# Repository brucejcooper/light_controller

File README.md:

# Light Switch firmware
This repo consists of the code that I'm using for my own home automation light switches.

### Theory of operation

1. Devices must operate independently.  If one of these breaks, I don't want the whole house to go dark.
1. Power consumption must be minimised, especially when the light is off.
1. I must be able to control lights via a home automation system (home assistant, or equivalent)
1. It should be as cheap as possible to produce.

So the idea is that none of these devices will have WiFi or ethernet themselves.  That would consume too much current.  Instead, We will use the DALI protocol, which is baked into the transformers that I'll be using for my home.  The circuit for driving a dali signal is very simple, with the exception of isolated power (needed to make the device safe in the presence of a 220V AC wire).  All isolated power systems that I'm aware of use a large amount of quiescent current (on the order of 10s of mA).  This would overload the DALI power supply. 

# Tech notes

## Downloading AVR compiler for attiny 0 series
The default avr-gcc installed by ubuntu doesn't do the 0 series, so I'm stealing the one that Arduino uses

```bash
wget http://downloads.arduino.cc/tools/avr-gcc-7.3.0-atmel3.6.1-arduino7-x86_64-pc-linux-gnu.tar.bz2 -q -O- | bzcat | tar xv
```

This will create a avr-gcc toolchain in the directory `avr` - The Makefile is set up to use this by default.  You can also just run `make download_gcc` to get it.  I will make this query the arduino repository for the latest version in a later update.

This repository is an experiment I am conducting on how best to do a circuit implemented a million times before.  a light switch dimmer (trailing edge). The idea here is to make something that is both efficient and cheap to build.

[Shelly](https://shelly.cloud) produces good, cheap devices, but I'm worried about their vampiric current draw.

# On Matter
I experimented with matter, and got it working quite well.  I have a couple of problems however
1. Its pretty power hungry to run a radio transmitter.  It will use 10s of milliamps for short periods, fairly often.  We might be able to get away with a large capacitor, or we might be able to set it up as a SED so that they wake up less often. Or we might run a second power cble to supply more power.  Seems like overkill, however
2. Transactions can take some time.  Each time a session is set up, a new encryption channel is set up.  This takes time.  I was seeing hundreds of milliseconds of latency, which becomes noticeable.  Now a few hundred milliseconds for a voice command is fine, but when I push a button, I want the light to react instantly.
3. NRF chipsets cost more, and require more external parts

# Keeping it simple
So here's what I've landed on. I want the switches themselves to be as simple as possible, and to use as little power as possible.  It should be sleeping 99.9999% of the time. It shouldn't wake up unless its got something to do (i.e. if something else transmits that is no reason for the rest of the devices to wake up and listen)

In order to facilitate this, configuration will be done via an OOB mechanism, rather than via the DALI protocol, as this will mean that the devices don't need to listen all the time. 

1. The device will sleep all the time
1. Wake up source is NFC, UPDI, or a button press.
1. Do what you need to do, go back to sleep once the button is released.

I have discovered that taking an event driven coding mechanism wastes flash.  I've now simplified it to just do things sequentially in the main loop, and deal with the fact that transmit and receive can take milliseconds.  Button timings will be much longer than this anway, so we can just take a quick break.  In some circumstances, this happens during a debounce period anyway.

The consequence of this is that all configuration needs to be done locally. The idea is to attach a NFC loop that will listen, wake up the chip, and boot into a bootloader - The use of a bootloader allows us to flash over NFC as well.   NFC will also power the chip (temporarily) allowing the device to be configured before being connected to DALI bus.  (But how, we want NFC to work even after DALI is connected.  The chip will put out 2V, so a diode would cause an unacceptable voltage drop.  Do I need a Power Mux e.g TPS2116.  I probably do.  Luckily they are pretty cheap. 

A simpler way to do it is to just use UPDI - but this means adding some sort of connector to the case and also has the same multi-supply problem (which could be fixed with a diode or a switch).

## Bootloader

Needs a mechanism to automatically reboot the MCU when the NFC is being used - We could rely upon the main firmware to detect the field then reboot itself, but what if it crashes?  Maybe the WDT?

Each FD transition from high -> low (SRAM filled up) could be turned into a quick pulse on RESET (minimum requirement of 2.5us), using a monostable multivibrator (SN74LVC1G123).  The bootloader now boots each time a FD goes low, but we might need multiple transactions to flash the device. SRAM can only store 64 bytes at a time.  We don't want to boot into a half written flash, so perhaps the Bootloader needs to check an EEPROM value.  

If there were two slots, we could check if we're complete or not.  We'd repeatedly reboot into the old firmware until the last block was written. 

## WDT
Do I need a WDT?  Its probably a good idea.

# Pins
* 2 Voltage supply
* 1 Reset/UPDI
* 5 switches
* 2 DALI TX/RX
* 4 left over. Not quite enough for LEDs. 

GPIO expander for LEDs? Or just go to 20 pin package (which would also get us I2C). Attiny406 is $1.26.  Attiny404 is $1.05 so $0.21 difference. Much cheaper than a separate chip.

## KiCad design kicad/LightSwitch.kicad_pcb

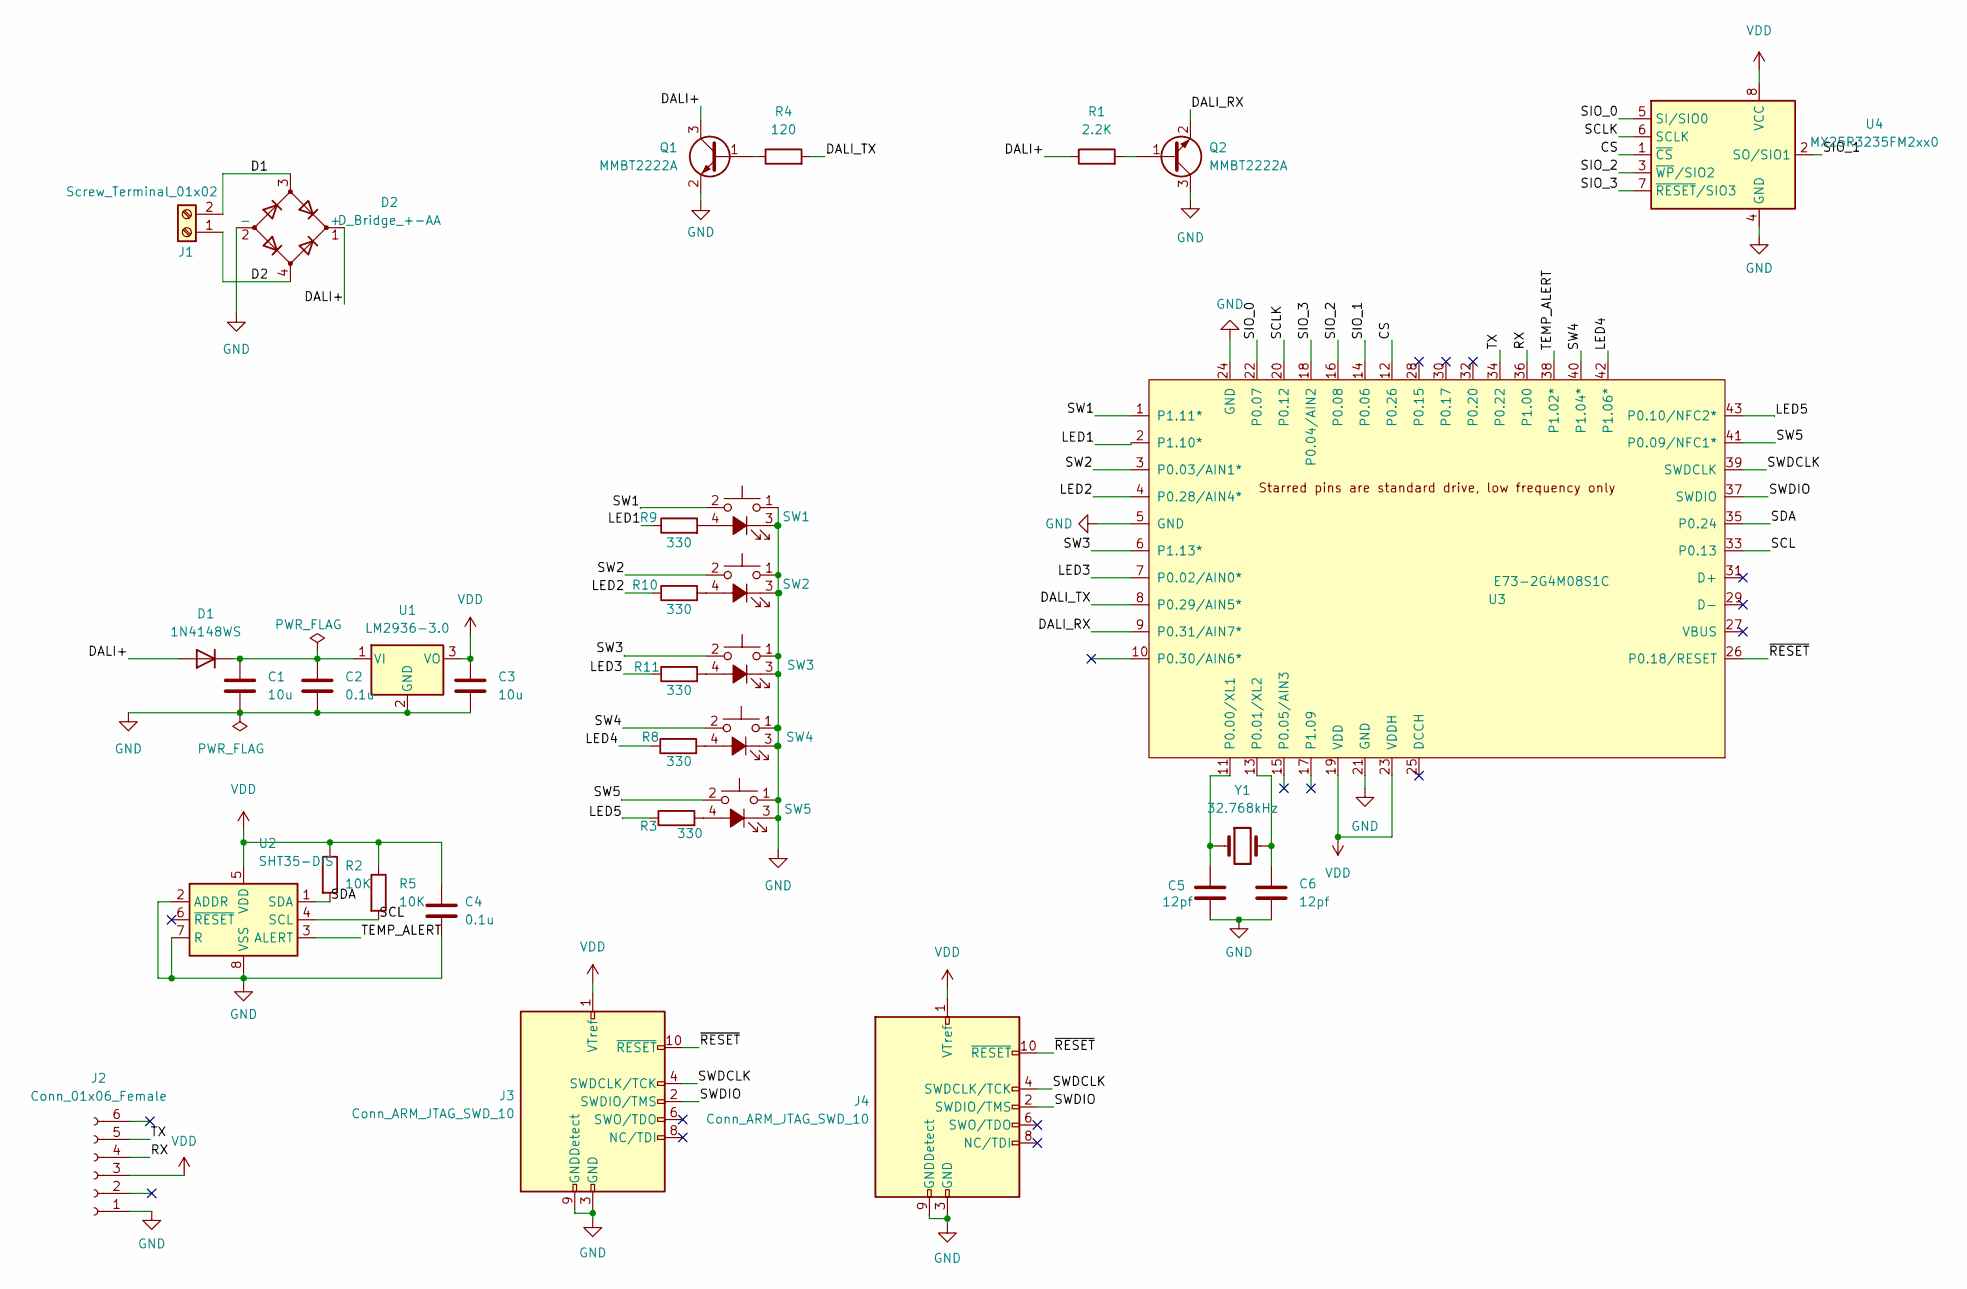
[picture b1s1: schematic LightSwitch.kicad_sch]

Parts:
C1, C3: 10u; C_0805_2012Metric
C2, C4: 0.1u; C_0805_2012Metric
C5, C6: 12pf; C_0805_2012Metric
D1: 1N4148WS; D_SOD-323
D2: D_Bridge_+-AA; SOIC245P670X290-4N
J1: Screw_Terminal_01x02; TerminalBlock_Phoenix_MKDS-1,5-2-5.08_1x02_P5.08mm_Horizont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
J2: Conn_01x06_Female; PinSocket_1x06_P2.54mm_Vertical
J3: Conn_ARM_JTAG_SWD_10; PinHeader_2x05_P1.27mm_Vertical_SMD
J4: Conn_ARM_JTAG_SWD_10; Tag-Connect_TC2050-IDC-NL_2x05_P1.27mm_Vertical
Q1, Q2: MMBT2222A; SOT-23
R1: 2.2K; R_0805_2012Metric
R2, R5: 10K; R_0805_2012Metric
R3, R8, R9, R10, R11: 330; R_0805_2012Metric
R4: 120; R_0805_2012Metric
SW1, SW2, SW3, SW4, SW5: SW_Push_LED; LED Pushbutton
U1: LM2936-3.0; TO-92_Inline
U2: SHT35-DIS; Sensirion_DFN-8-1EP_2.5x2.5mm_P0.5mm_EP1.1x1.7mm
U3: E73-2G4M08S1C
U4: MX25R3235FM2xx0; SOP-8_5.28x5.23mm_P1.27mm
Y1: 32.768kHz; Crystal_SMD_3215-2Pin_3.2x1.5mm

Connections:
/CS: U3.12 (P0.26), U4.1 (~CS)
/D1: D2.3, J1.2
/D2: D2.4, J1.1
/DALI+: D1.2 (A), D2.1 (+), Q1.3 (C), R1.1
/DALI_RX: Q2.2 (E), U3.9 (P0.31/AIN7*)
/DALI_TX: R4.2, U3.8 (P0.29/AIN5*)
/LED1: R9.1, U3.2 (P1.10*)
/LED2: R10.1, U3.4 (P0.28/AIN4*)
/LED3: R11.1, U3.7 (P0.02/AIN0*)
/LED4: R8.1, U3.42 (P1.06*)
/LED5: R3.1, U3.43 (P0.10/NFC2*)
/RX: J2.4, U3.36 (P1.00)
/SCL: R5.2, U2.4 (SCL), U3.33 (P0.13)
/SCLK: U3.20 (P0.12), U4.6 (SCLK)
/SDA: R2.2, U2.1 (SDA), U3.35 (P0.24)
/SIO_0: U3.22 (P0.07), U4.5 (SI/SIO0)
/SIO_1: U3.14 (P0.06), U4.2 (SO/SIO1)
/SIO_2: U3.16 (P0.08), U4.3 (~WP/SIO2)
/SIO_3: U3.18 (P0.04/AIN2), U4.7 (~RESET/SIO3)
/SW1: SW1.2, U3.1 (P1.11*)
/SW2: SW2.2, U3.3 (P0.03/AIN1*)
/SW3: SW3.2, U3.6 (P1.13*)
/SW4: SW4.2, U3.40 (P1.04*)
/SW5: SW5.2, U3.41 (P0.09/NFC1*)
/SWDCLK: J3.4 (SWDCLK/TCK), J4.4 (SWDCLK/TCK), U3.39 (SWDCLK)
/SWDIO: J3.2 (SWDIO/TMS), J4.2 (SWDIO/TMS), U3.37 (SWDIO)
/TEMP_ALERT: U2.3 (ALERT), U3.38 (P1.02*)
/TX: J2.5, U3.34 (P0.22)
/~RESET: J3.10 (~RESET), J4.10 (~RESET), U3.26 (P0.18/RESET)
GND: C1.2, C2.2, C3.2, C4.1, C5.2, C6.2, D2.2 (-), J2.1, J3.3 (GND), J3.5 (GND), J3.9 (GNDDetect), J4.3 (GND), J4.5 (GND), J4.9 (GNDDetect), Q1.2 (E), Q2.3 (C), SW1.1, SW1.3 (K), SW2.1, SW2.3 (K), SW3.1, SW3.3 (K), SW4.1, SW4.3 (K), SW5.1, SW5.3 (K), U1.2 (GND), U2.2 (ADDR), U2.7 (R), U2.8 (VSS), U2.9 (VSS), U3.5 (GND), U3.21 (GND), U3.24 (GND), U4.4 (GND)
unnamed: C1.1, C2.1, D1.1 (K), U1.1 (VI)
unnamed: C5.1, U3.11 (P0.00/XL1), Y1.1
unnamed: C6.1, U3.13 (P0.01/XL2), Y1.2
unnamed: Q1.1 (B), R4.1
unnamed: Q2.1 (B), R1.2
unnamed: R3.2, SW5.4 (A)
unnamed: R8.2, SW4.4 (A)
unnamed: R9.2, SW1.4 (A)
unnamed: R10.2, SW2.4 (A)
unnamed: R11.2, SW3.4 (A)
VDD: C3.1, C4.2, J2.3, J3.1 (VTref), J4.1 (VTref), R2.1, R5.1, U1.3 (VO), U2.5 (VDD), U3.19 (VDD), U3.23 (VDDH), U4.8 (VCC)

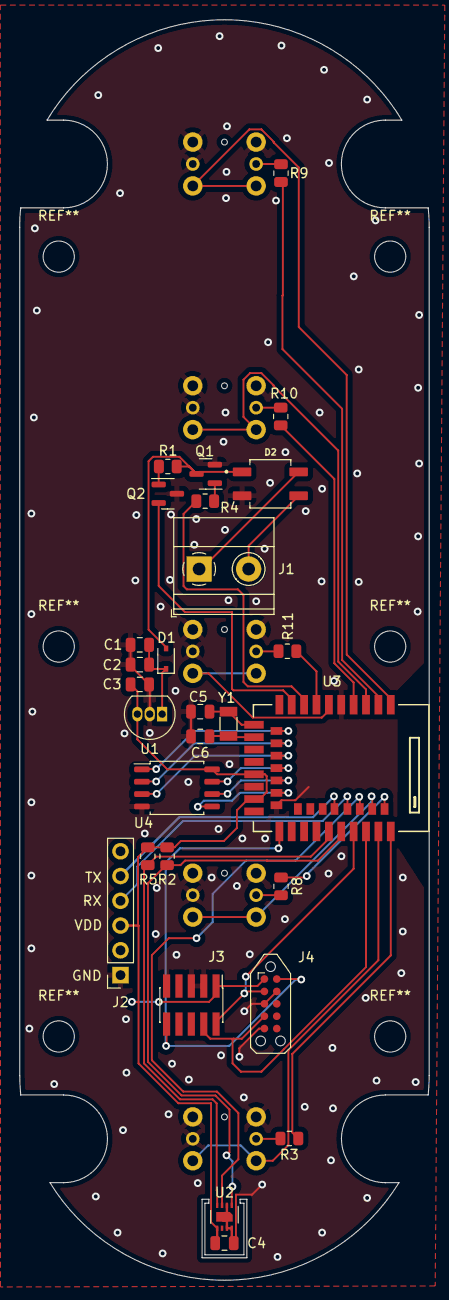
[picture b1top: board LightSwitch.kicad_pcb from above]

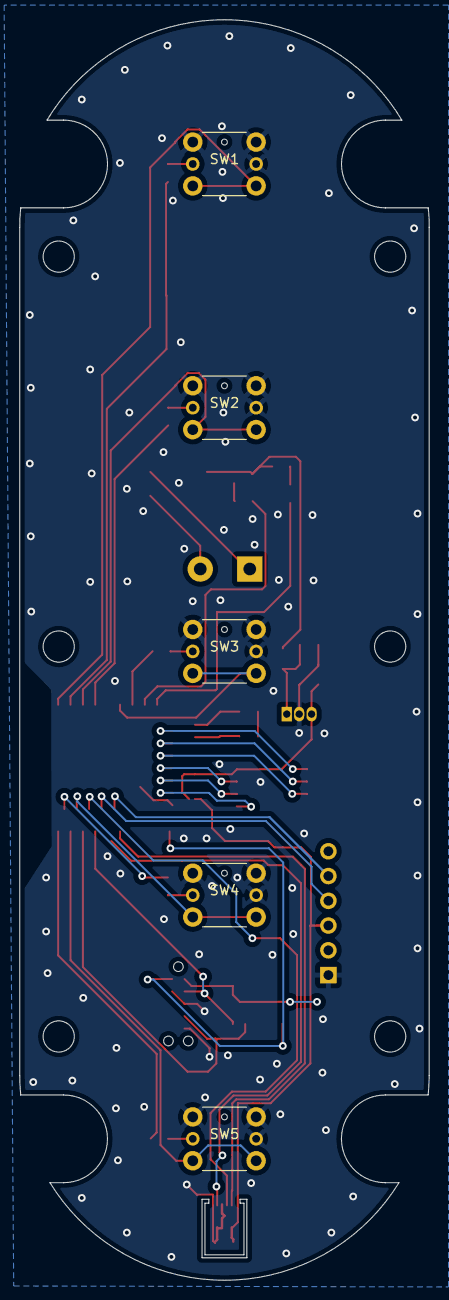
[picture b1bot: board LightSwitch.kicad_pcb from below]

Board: 2 copper layers, 42.0 x 129.3 mm, 33 parts (5 on the bottom side), 41 nets.

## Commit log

2021-12-05 Before I move to comparator approach
2021-12-05 Works with diode clamped input
2021-12-06 Added Circuit
2021-12-06 Some small circuit changes
2021-12-06 more circuit changes
2021-12-06 Doco
2022-04-29 Switch to Attiny804, and got it working with its own (stolen from arduino) compiler
2022-05-02 Doco update
2022-06-10 moving back to personal computer
2022-06-12 Working button debouncing, and written (but not tested) DALI
2022-06-13 Fixed clock, and made DALI transmission use a timer
2022-06-13 Added collision detection, and the start of receive
2022-06-18 Added an algorithm for reading
2022-06-19 Clean up code
2022-06-19 Changed read approach to use TCB0
2022-06-19 Moved DALI read and write into separate files, and added some safeguards
2022-07-02 Parking stuff, so I can contemplate the use of a nrf52840 _with_ DALI
2022-08-08 Updated with NRF52840 version. Modded since sending to OSHPark
2022-08-25 Added double click support, and Serial logging
2022-08-26 Changed DALI transmit to use timer based bit flips of the GPIO
2022-09-04 Protoboard version works - Next - Move to using comparator
2022-09-05 Switch to using voltage divider for reading, rather than a transistor. This gives us a specific voltage threshold to work with
2022-09-19 Set up for bit state based change - But will test 1M divider first
2022-09-24 Staging for move to Raspberry Pi
2022-09-26 Got USB bridge working for Transmit. Made console take input commands
2022-10-02 Working send and receive for USB version
2022-10-08 latect schematic
2022-12-05 Fixed bugs in timing. USB variant now looking a lot like the normal one... Will merge later
2022-12-13 Major rewrite of state machine, with extensive use of callbacks
2022-12-13 Re-ordered source and makefile
2022-12-19 Movin back to desktop
2022-12-21 Bug fixes
2022-12-21 More bug fixes. Now dealing with timeout accuracy
2022-12-21 more bug fixes
2022-12-23 Works pretty well now. Pushing the button toggles the configured lamp. Next is getting it to be discoverable
2023-01-27 Parking before yet another rewrite/simplification
2023-01-30 stashing before trhing something simpler
2023-01-30 Got simple version going, and got it under 2K
2023-01-30 Added delay between write and read, as this was causing issues
2023-01-31 Added sleep
2023-01-31 pretty minimal now
2023-01-31 Just going silly on the flash optimisation now.. Went back to enum based states as it uses lots less instructions than function pointer based
2023-02-02 Got dimming working
2023-02-04 Fixed bugs caused by missing ISRs when sleeping
2023-02-04 Removed some redundant code
2023-02-05 removed logging
2023-02-06 Fixed bug causing some button presses to be ignored. it was polling after being woken up, which caused a debuonce problem
2023-02-08 Added explicit debouncing
2023-03-19 Bootloader
2023-03-19 Refactoring NFC stuff. might park it, as it is too susceptible to metal interference. Will experiment again wth BLE
